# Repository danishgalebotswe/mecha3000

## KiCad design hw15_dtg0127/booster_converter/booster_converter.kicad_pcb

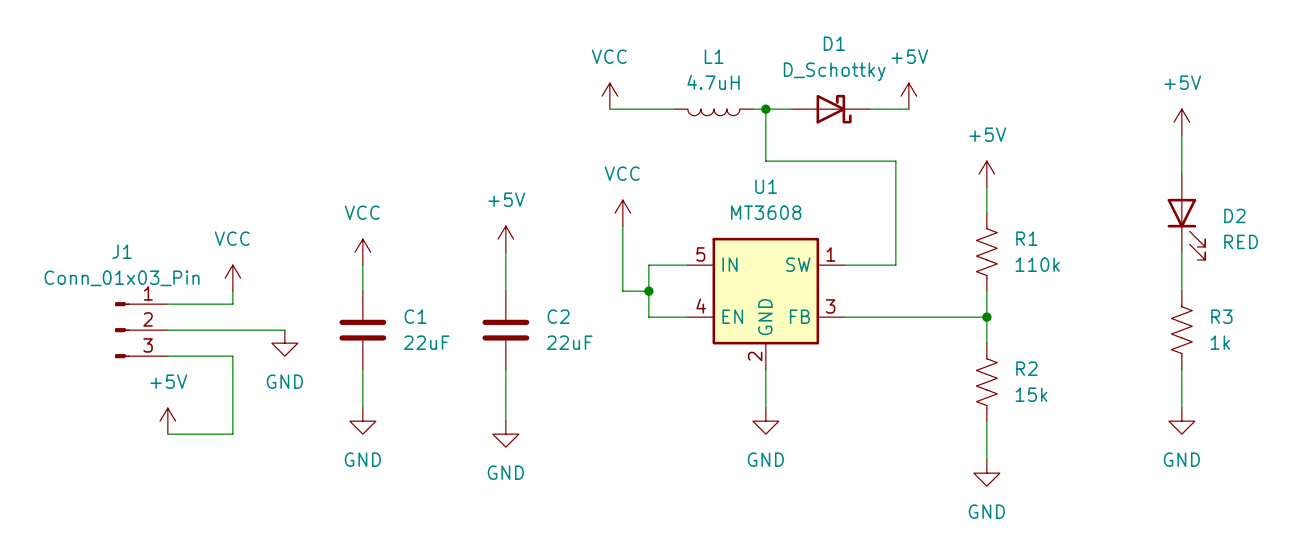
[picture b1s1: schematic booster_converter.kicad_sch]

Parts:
C1, C2: 22uF; CP_Elec_6.3x3
D1: D_Schottky; D_3220_8050Metric_Pad2.65x5.15mm_HandSolder
D2: RED; LED_0201_0603Metric
J1: Conn_01x03_Pin; PinSocket_1x03_P2.54mm_Vertical
L1: 4.7uH; L_6.3x6.3_H3
R1: 110k; R_0201_0603Metric
R2: 15k; R_0201_0603Metric
R3: 1k; R_0201_0603Metric
U1: MT3608; SOT-23-6

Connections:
+5V: C2.1, D1.1 (K), D2.2 (A), J1.3, R1.1
GND: C1.2, C2.2, J1.2, R2.2, R3.2, U1.2 (GND)
unnamed: D1.2 (A), L1.1, U1.1 (SW)
unnamed: D2.1 (K), R3.1
unnamed: R1.2, R2.1, U1.3 (FB)
VCC: C1.1, J1.1, L1.2, U1.4 (EN), U1.5 (IN)

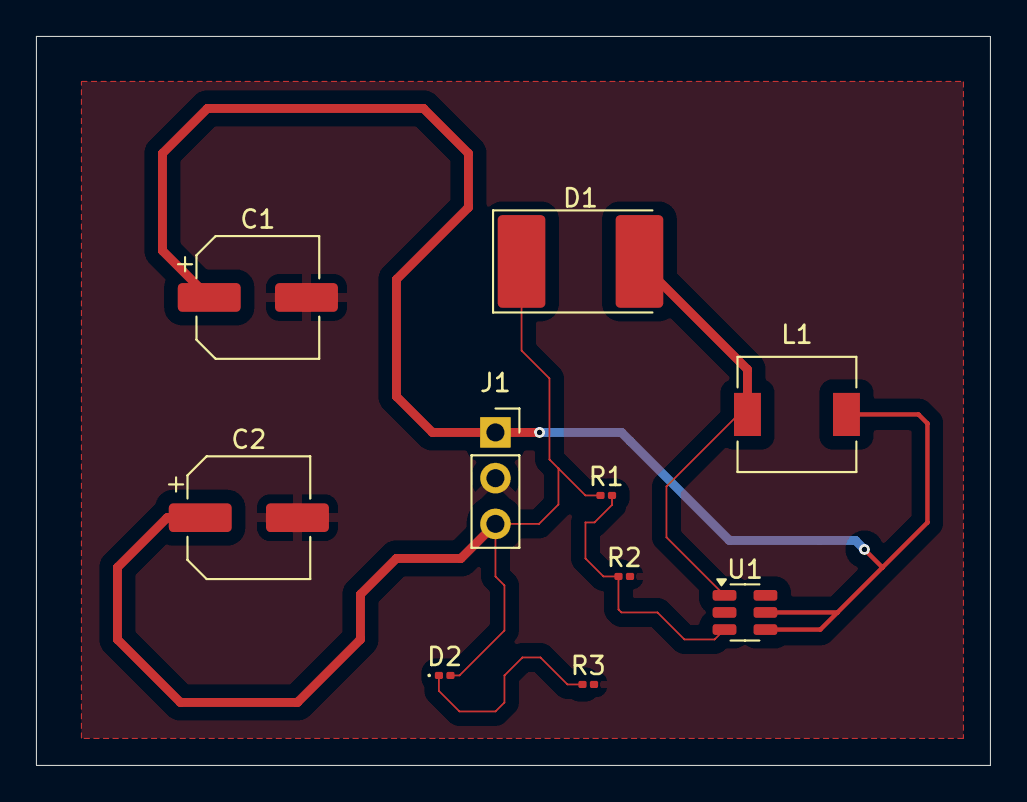
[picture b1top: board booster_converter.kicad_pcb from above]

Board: 2 copper layers, 53.0 x 40.5 mm, 10 parts (0 on the bottom side), 6 nets.

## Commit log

2025-04-08 hw3 files
2025-04-09 got the LED to switch on when the button is pressed
2025-04-09 completed hw3, need to record video
2025-04-14 started hw4
2025-04-14 working code
2025-04-17 hw5 stuff
2025-04-17 hw5 working
2025-04-19 created hw6 and finished it
2025-04-24 started hw7
2025-04-24 finished hw7
2025-04-29 hw8 complete
2025-04-29 moving files to hw8 folder
2025-04-29 started hw9
2025-04-29 getting user input
2025-04-29 line break for prompt
2025-04-29 added spacing for number 1
2025-04-29 removed line break from scanf
2025-04-29 getting voltage works
2025-05-15 started hw10
2025-05-15 added moving average filter
2025-05-16 started hw11
2025-05-26 first initialization for camera hw
2025-05-27 finished hw12
2025-05-27 initialized hw13
2025-05-27 not working oled and accel reader
2025-06-01 hw13 working-ish
2025-06-01 robot cad
2025-06-03 hw15 works
2025-06-03 hw16 not tested
